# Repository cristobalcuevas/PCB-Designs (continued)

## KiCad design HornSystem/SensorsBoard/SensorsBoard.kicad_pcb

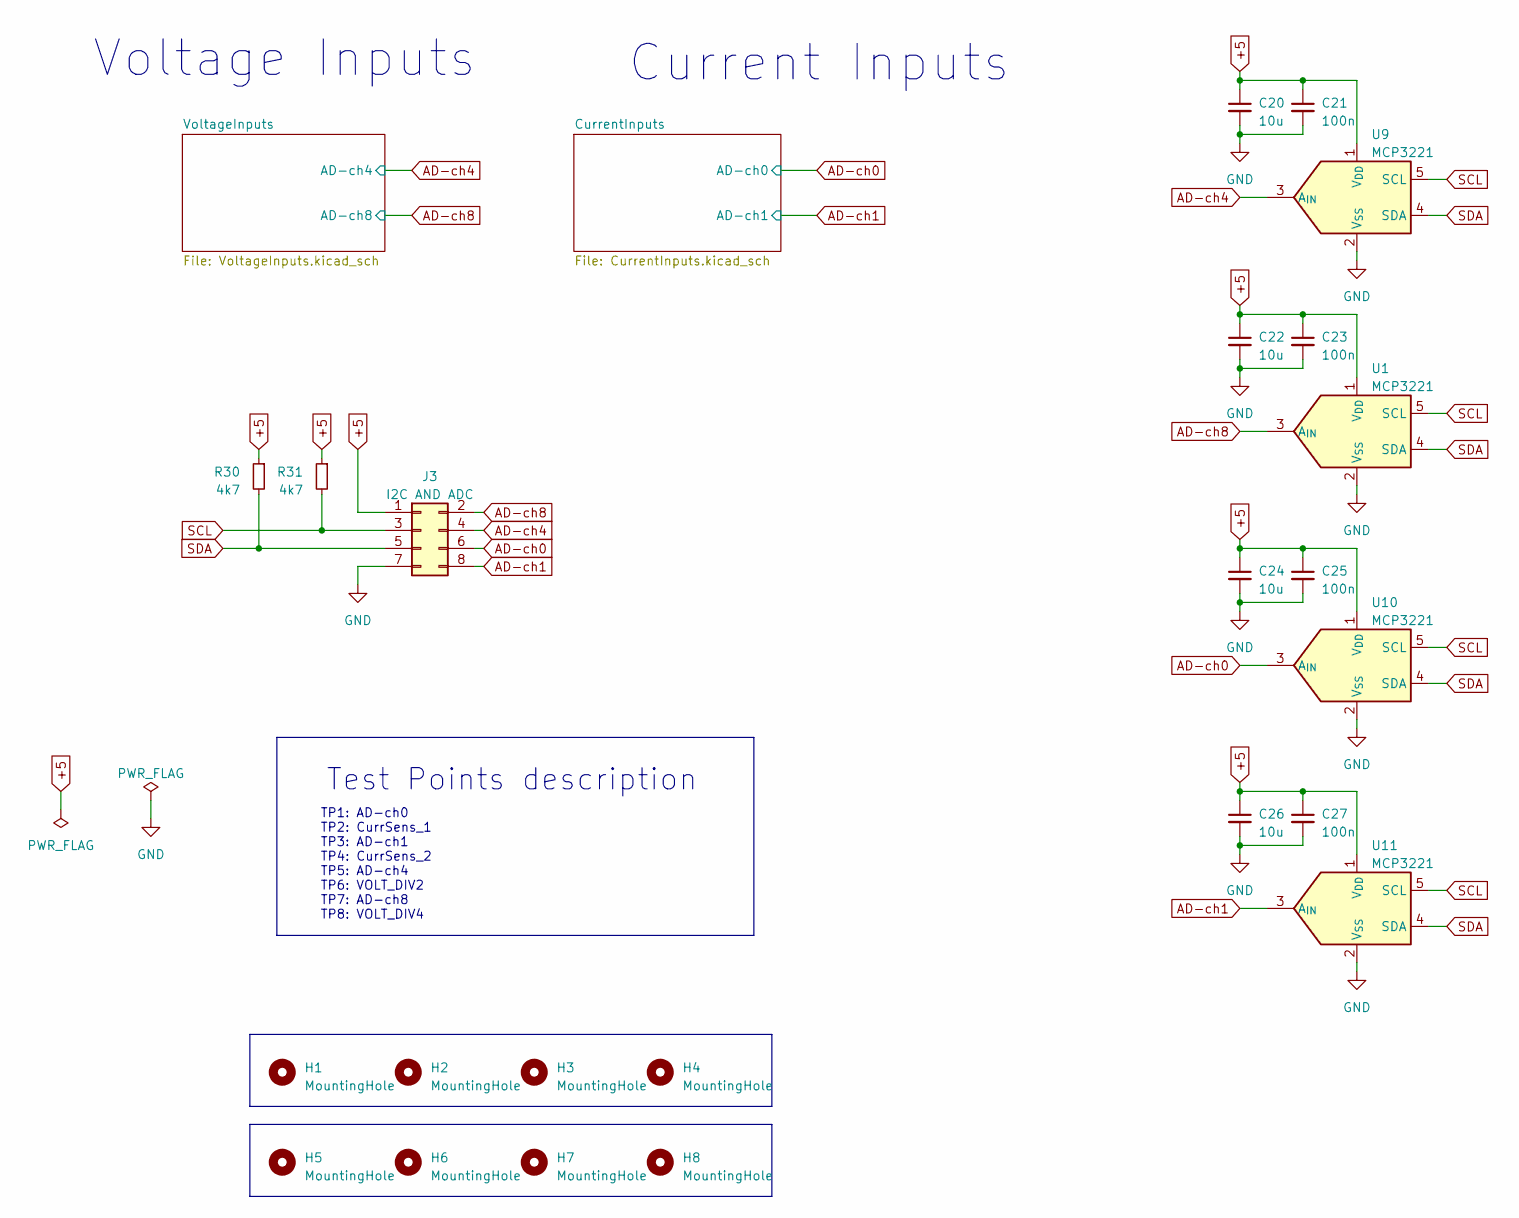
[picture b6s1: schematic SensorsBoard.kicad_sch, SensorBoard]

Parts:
C20, C22, C24, C26: 10u; C_0805_2012Metric; JLCPCB Part C380331
C21, C23, C25, C27: 100n; C_0805_2012Metric; JLCPCB Part C710457
H1, H2, H3, H4, H5, H6, H7, H8: MountingHole; MountingHole_3.2mm_M3
J3: I2C AND ADC; PinHeader_2x04_P2.54mm_Vertical
R30, R31: 4k7; R_0805_2012Metric; JLCPCB Part C2759288
U1, U9, U10, U11: MCP3221; SOT-23-5

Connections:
+5: C20.1, C21.1, C22.1, C23.1, C24.1, C25.1, C26.1, C27.1, J3.1, R30.1, R31.1, U1.1 (V_{DD}), U9.1 (V_{DD}), U10.1 (V_{DD}), U11.1 (V_{DD}); also elsewhere on the board
AD-ch0: J3.6, U10.3 (A_{IN}); also elsewhere on the board
AD-ch1: J3.8, U11.3 (A_{IN}); also elsewhere on the board
AD-ch4: J3.4, U9.3 (A_{IN}); also elsewhere on the board
AD-ch8: J3.2, U1.3 (A_{IN}); also elsewhere on the board
GND: C20.2, C21.2, C22.2, C23.2, C24.2, C25.2, C26.2, C27.2, J3.7, U1.2 (V_{SS}), U9.2 (V_{SS}), U10.2 (V_{SS}), U11.2 (V_{SS}); also elsewhere on the board
SCL: J3.3, R31.2, U1.5 (SCL), U9.5 (SCL), U10.5 (SCL), U11.5 (SCL)
SDA: J3.5, R30.2, U1.4 (SDA), U9.4 (SDA), U10.4 (SDA), U11.4 (SDA)

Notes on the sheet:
Current Inputs
Test Points description
TP1: AD-ch0 TP2: CurrSens_1 TP3: AD-ch1 TP4: CurrSens_2 TP5: AD-ch4 TP6: VOLT_DIV2 TP7: AD-ch8 TP8: VOLT_DIV4
Voltage Inputs

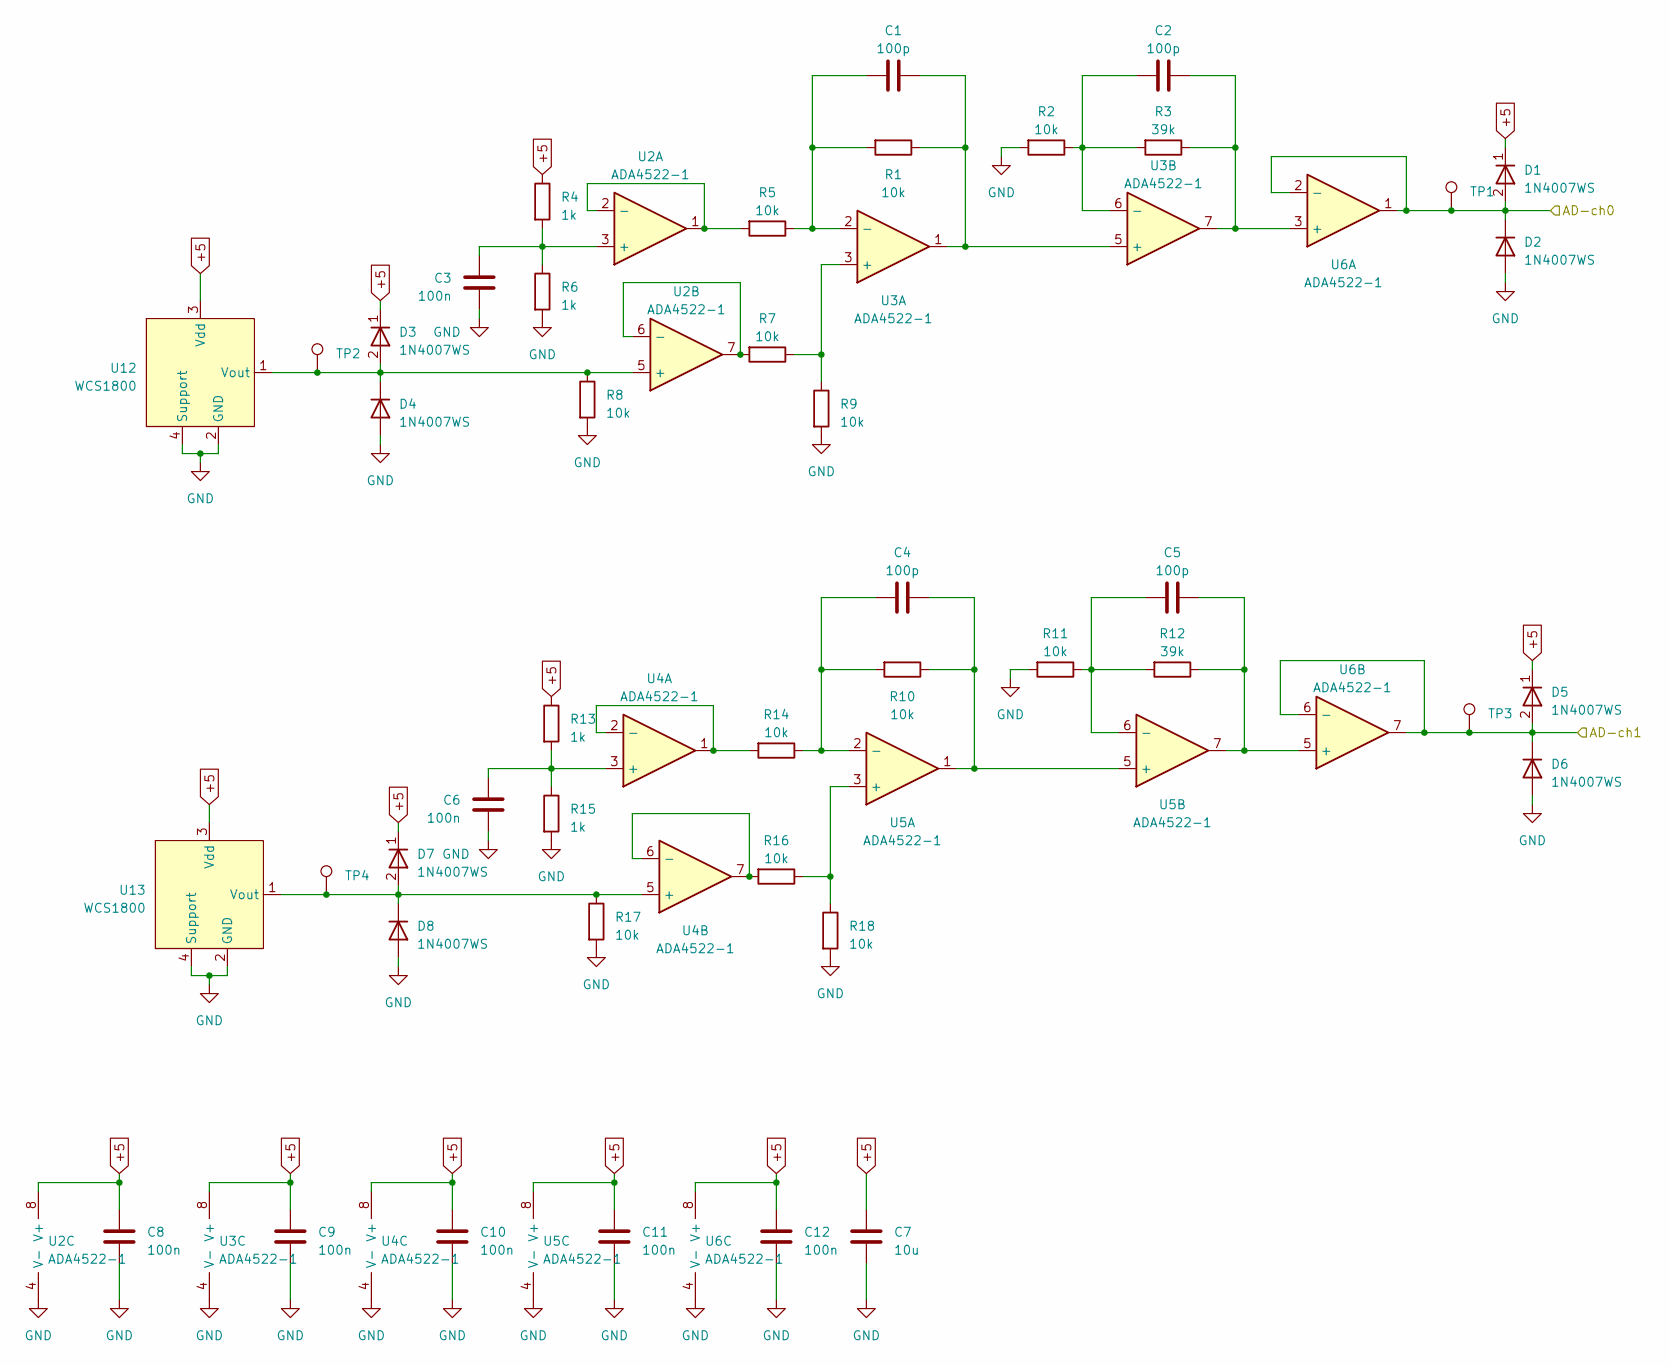
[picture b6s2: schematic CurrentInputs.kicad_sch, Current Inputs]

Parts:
C1, C2, C4, C5: 100p; C_0805_2012Metric; JLCPCB Part C2691714
C3, C6, C8, C9, C10, C11, C12: 100n; C_0805_2012Metric; JLCPCB Part C710457
C7: 10u; C_0805_2012Metric; JLCPCB Part C380331
D1, D2, D3, D4, D5, D6, D7, D8: 1N4007WS; D_SOD-323; JLCPCB Part C193404
R1, R2, R5, R7, R8, R9, R10, R11, R14, R16, R17, R18: 10k; R_0805_2012Metric; JLCPCB Part C212284
R3, R12: 39k; R_0805_2012Metric; JLCPCB Part C139877
R4, R6, R13, R15: 1k; R_0805_2012Metric; JLCPCB Part C335229
TP1, TP2, TP3, TP4: TestPoint; TestPoint_Pad_D1.0mm
U2, U3, U4, U5, U6: ADA4522-1; MSOP-8_3x3mm_P0.65mm; JLCPCB Part C127898
U12, U13: WCS1800

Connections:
+5: C7.1, C8.1, C9.1, C10.1, C11.1, C12.1, D1.1 (K), D3.1 (K), D5.1 (K), D7.1 (K), R4.1, R13.1, U2.8 (V+), U3.8 (V+), U4.8 (V+), U5.8 (V+), U6.8 (V+), U12.3 (Vdd), U13.3 (Vdd); also elsewhere on the board
AD-ch0: D1.2 (A), D2.1 (K), TP1.1, U6.1, U6.2 (-); also elsewhere on the board
AD-ch1: D5.2 (A), D6.1 (K), TP3.1, U6.6 (-), U6.7; also elsewhere on the board
GND: C3.2, C6.2, C7.2, C8.2, C9.2, C10.2, C11.2, C12.2, D2.2 (A), D4.2 (A), D6.2 (A), D8.2 (A), R2.2, R6.2, R8.2, R9.2, R11.2, R15.2, R17.2, R18.2, U2.4 (V-), U3.4 (V-), U4.4 (V-), U5.4 (V-), U6.4 (V-), U12.2 (GND), U12.4 (Support), U13.2 (GND), U13.4 (Support); also elsewhere on the board
unnamed: D3.2 (A), D4.1 (K), R8.1, TP2.1, U2.5 (+), U12.1 (Vout)
unnamed: D7.2 (A), D8.1 (K), R17.1, TP4.1, U4.5 (+), U13.1 (Vout)
unnamed: C3.1, R4.2, R6.1, U2.3 (+)
unnamed: R5.2, U2.1, U2.2 (-)
unnamed: R7.2, U2.6 (-), U2.7
unnamed: R7.1, R9.1, U3.3 (+)
unnamed: C1.1, R1.2, R5.1, U3.2 (-)
unnamed: C1.2, R1.1, U3.1, U3.5 (+)
unnamed: C2.1, R2.1, R3.2, U3.6 (-)
unnamed: C6.1, R13.2, R15.1, U4.3 (+)
unnamed: R14.2, U4.1, U4.2 (-)
unnamed: R16.2, U4.6 (-), U4.7
unnamed: R16.1, R18.1, U5.3 (+)
unnamed: C4.1, R10.2, R14.1, U5.2 (-)
unnamed: C4.2, R10.1, U5.1, U5.5 (+)
unnamed: C5.1, R11.1, R12.2, U5.6 (-)
unnamed: C2.2, R3.1, U3.7, U6.3 (+)
unnamed: C5.2, R12.1, U5.7, U6.5 (+)

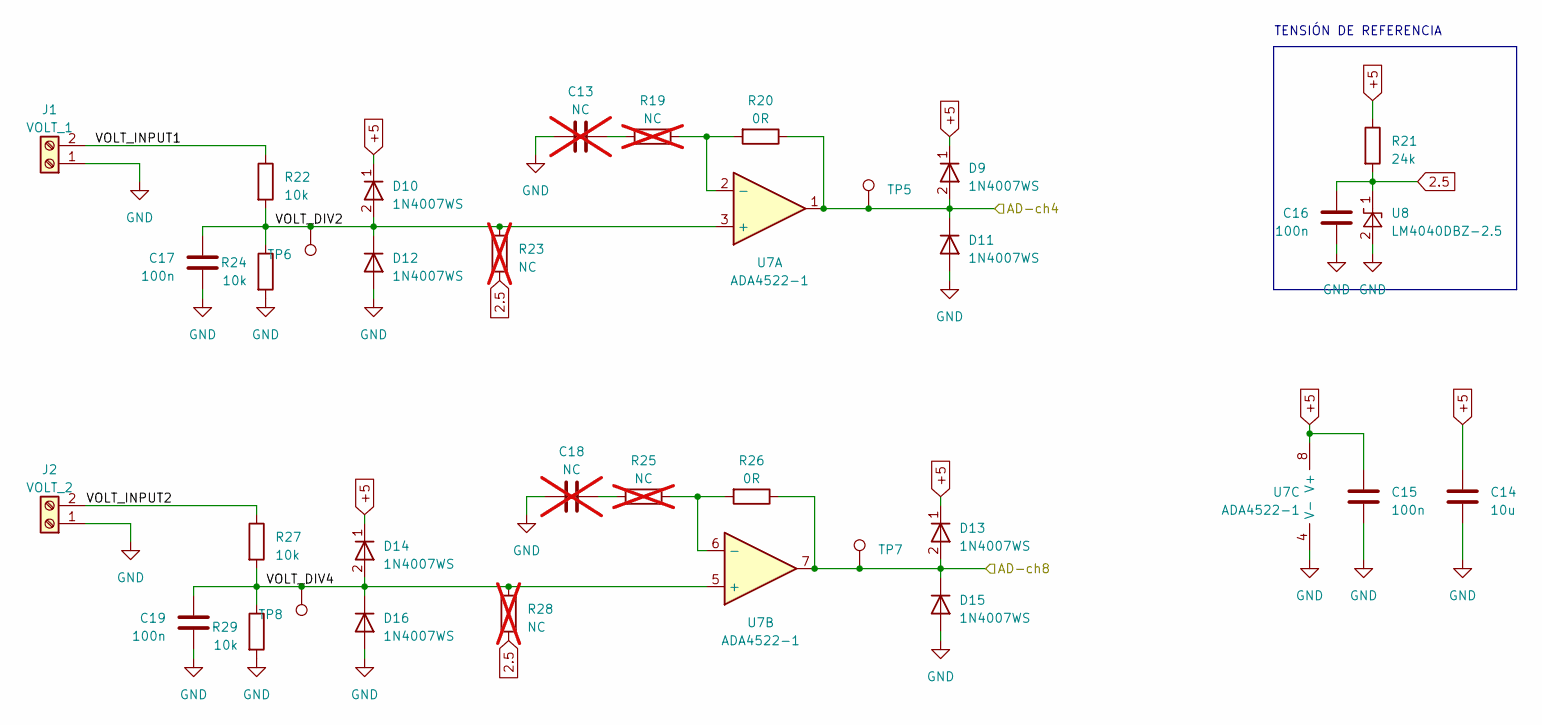
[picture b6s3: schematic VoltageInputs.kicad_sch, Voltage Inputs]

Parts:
C13, C18: NC; C_0805_2012Metric; not fitted
C14: 10u; C_0805_2012Metric; JLCPCB Part C380331
C15, C16, C17, C19: 100n; C_0805_2012Metric; JLCPCB Part C710457
D9, D10, D11, D12, D13, D14, D15, D16: 1N4007WS; D_SOD-323; JLCPCB Part C193404
J1: VOLT_1; TerminalBlock_Phoenix_PT-1,5-2-3.5-H_1x02_P3.50mm_Horizontal; JLCPCB Part C474892
J2: VOLT_2; TerminalBlock_Phoenix_PT-1,5-2-3.5-H_1x02_P3.50mm_Horizontal; JLCPCB Part C474892
R19, R23, R25, R28: NC; R_0805_2012Metric; not fitted
R20, R26: 0R; R_0805_2012Metric; JLCPCB Part C2907288
R21: 24k; R_0805_2012Metric; JLCPCB Part C286604
R22, R24, R27, R29: 10k; R_0805_2012Metric; JLCPCB Part C212284
TP5, TP6, TP7, TP8: TestPoint; TestPoint_Pad_D1.0mm
U7: ADA4522-1; MSOP-8_3x3mm_P0.65mm; JLCPCB Part C127898
U8: LM4040DBZ-2.5; SOT-23; JLCPCB Part C131939

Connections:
2.5: C16.2, R21.2, R23.2, R28.2, U8.1 (K)
+5: C14.1, C15.1, D9.1 (K), D10.1 (K), D13.1 (K), D14.1 (K), R21.1, U7.8 (V+); also elsewhere on the board
/VoltageInputs/VOLT_DIV2: C17.1, D10.2 (A), D12.1 (K), R22.2, R23.1, R24.1, TP6.1, U7.3 (+)
/VoltageInputs/VOLT_DIV4: C19.1, D14.2 (A), D16.1 (K), R27.2, R28.1, R29.1, TP8.1, U7.5 (+)
/VoltageInputs/VOLT_INPUT1: J1.2, R22.1
/VoltageInputs/VOLT_INPUT2: J2.2, R27.1
AD-ch4: D9.2 (A), D11.1 (K), R20.1, TP5.1, U7.1; also elsewhere on the board
AD-ch8: D13.2 (A), D15.1 (K), R26.1, TP7.1, U7.7; also elsewhere on the board
GND: C13.2, C14.2, C15.2, C16.1, C17.2, C18.2, C19.2, D11.2 (A), D12.2 (A), D15.2 (A), D16.2 (A), J1.1, J2.1, R24.2, R29.2, U7.4 (V-), U8.2 (A); also elsewhere on the board
unnamed: C13.1, R19.2
unnamed: C18.1, R25.2
unnamed: R19.1, R20.2, U7.2 (-)
unnamed: R25.1, R26.2, U7.6 (-)

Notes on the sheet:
TENSIÓN DE REFERENCIA

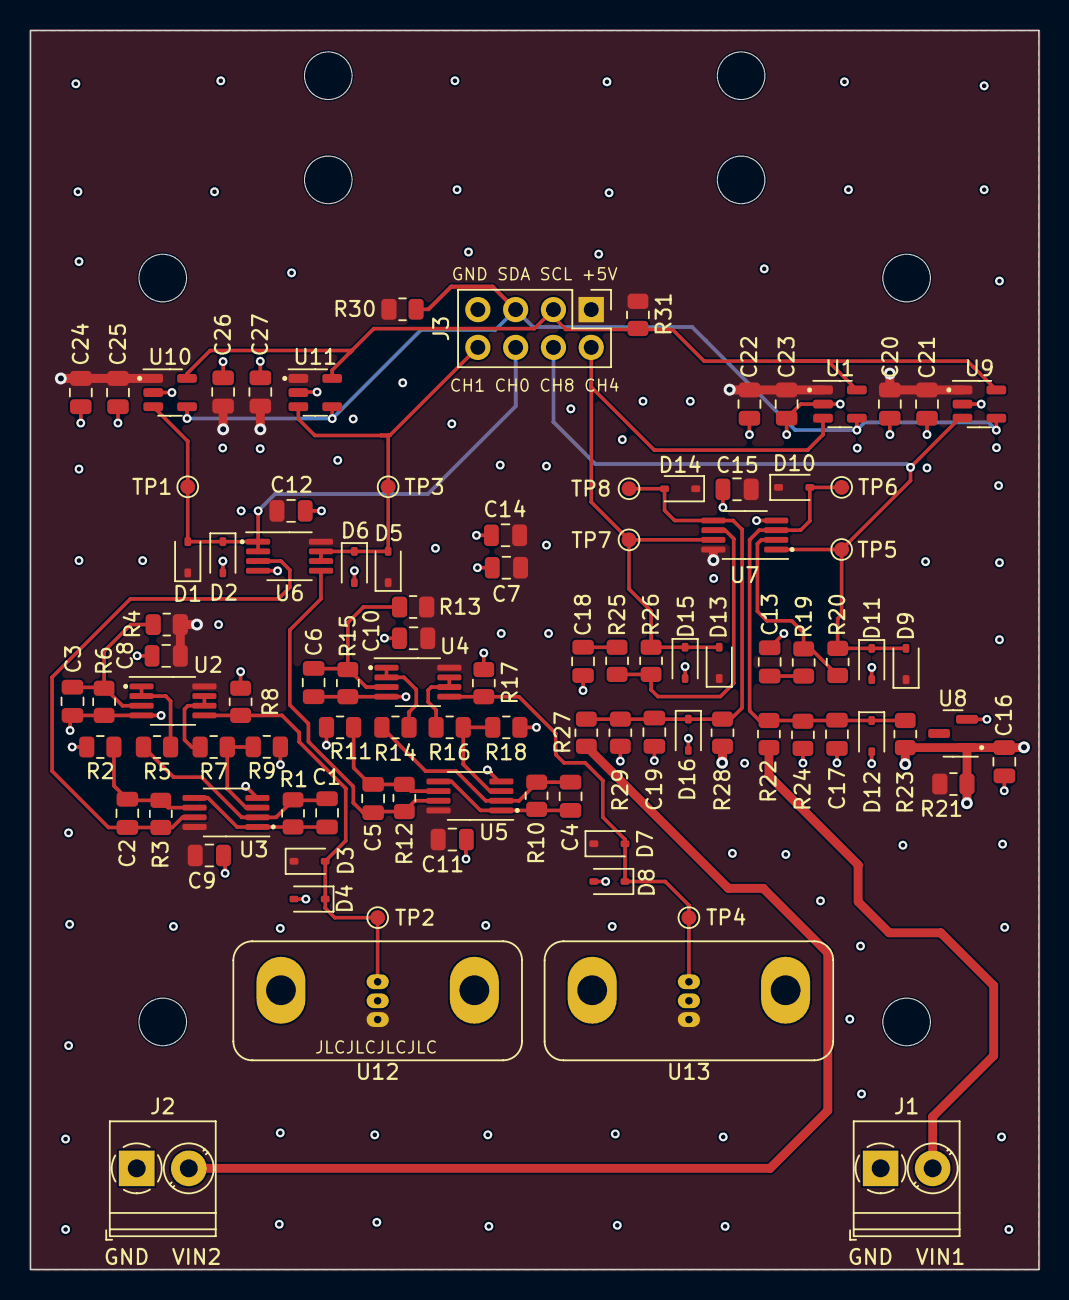
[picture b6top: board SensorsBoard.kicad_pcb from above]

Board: 4 copper layers, 67.8 x 83.3 mm, 106 parts (0 on the bottom side), 35 nets.

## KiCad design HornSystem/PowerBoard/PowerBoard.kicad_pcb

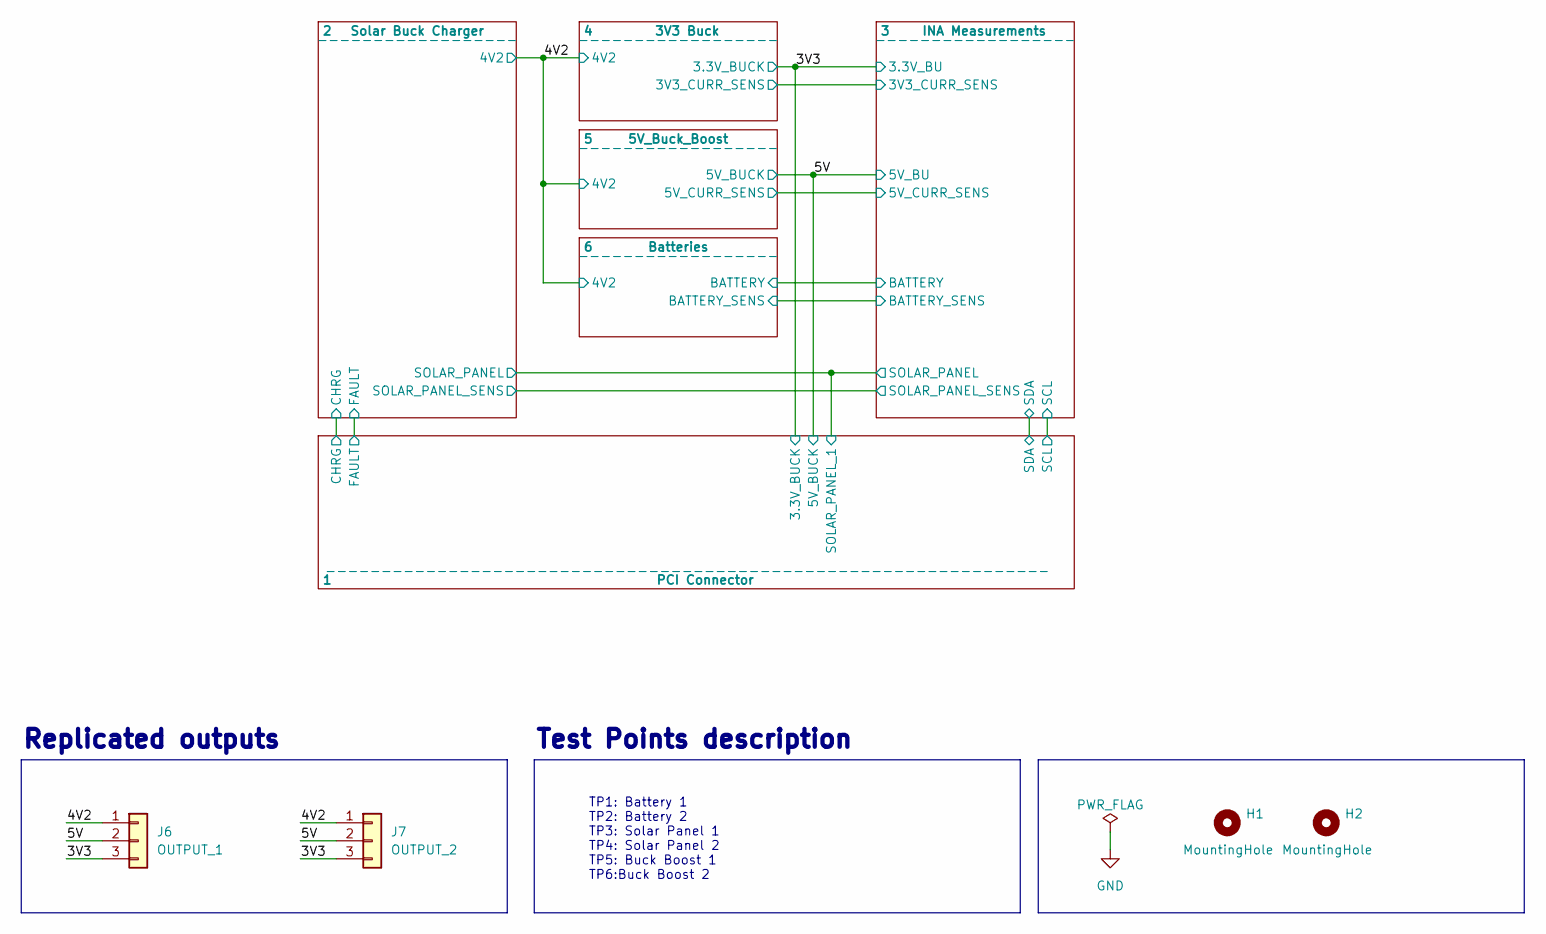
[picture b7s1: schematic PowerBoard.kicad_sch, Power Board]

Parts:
H1, H2: MountingHole; MountingHole_2.1mm
J6: OUTPUT_1; PinHeader_1x03_P2.54mm_Vertical
J7: OUTPUT_2; PinHeader_1x03_P2.54mm_Vertical

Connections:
5V_BUCK: J6.2, J7.2; also elsewhere on the board
/3V3: J6.3, J7.3; also elsewhere on the board
/4V2: J6.1, J7.1; also elsewhere on the board

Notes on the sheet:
TP1: Battery 1 TP2: Battery 2 TP3: Solar Panel 1 TP4: Solar Panel 2 TP5: Buck Boost 1 TP6:Buck Boost 2
Replicated outputs
Test Points description

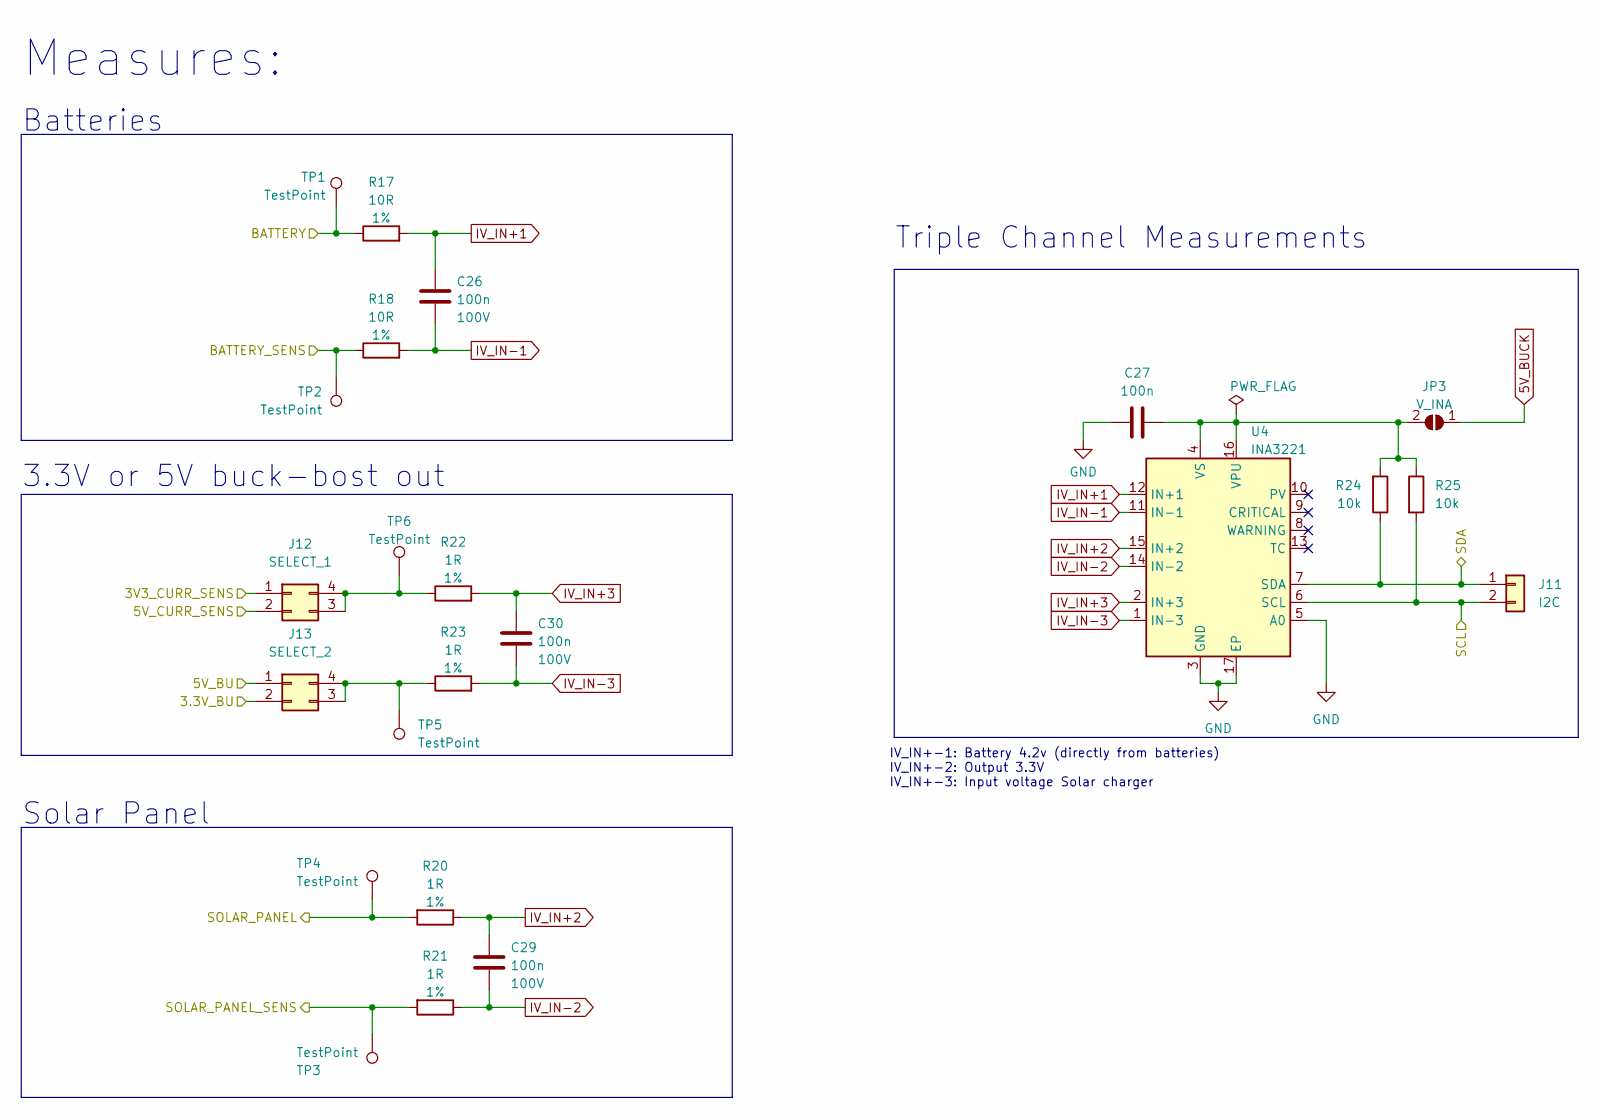
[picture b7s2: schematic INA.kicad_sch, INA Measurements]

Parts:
C26, C27, C29, C30: 100n; C_0805_2012Metric; Voltage 100V; JLCPCB Part C710457
J11: I2C; PinHeader_1x02_P2.54mm_Vertical
J12: SELECT_1; PinHeader_2x02_P2.54mm_Vertical
J13: SELECT_2; PinHeader_2x02_P2.54mm_Vertical
JP3: V_INA; SolderJumper-2_P1.3mm_Open_RoundedPad1.0x1.5mm
R17, R18: 10R; R_0805_2012Metric; Tolerance 1%; JLCPCB Part C17415
R20, R21, R22, R23: 1R; R_0805_2012Metric; Tolerance 1%; JLCPCB Part C25271
R24, R25: 10k; R_0805_2012Metric; JLCPCB Part RMS10FT1002
TP1, TP2, TP3, TP4, TP5, TP6: TestPoint; TestPoint_Pad_D1.0mm
U4: INA3221; Texas_RGV_S-PVQFN-N16_EP2.1x2.1mm; JLCPCB Part C181255

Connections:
5V_BUCK: J13.1, JP3.1 (A); also elsewhere on the board
/3V3: J13.2; also elsewhere on the board
/3V3 Buck/3V3_CURR_SENS: J12.1; also elsewhere on the board
/4V2: R17.1, TP1.1; also elsewhere on the board
/5V_Buck_Boost/5V_CURR_SENS: J12.2; also elsewhere on the board
/Batteries/BATTERY_SENS: R18.1, TP2.1; also elsewhere on the board
/INA Measurements/SCL: J11.2, R25.2, U4.6 (SCL); also elsewhere on the board
/INA Measurements/SDA: J11.1, R24.1, U4.7 (SDA); also elsewhere on the board
/INA Measurements/SOLAR_PANEL: R20.2, TP4.1; also elsewhere on the board
/INA Measurements/SOLAR_PANEL_SENS: R21.2, TP3.1; also elsewhere on the board
GND: C27.2, U4.3 (GND), U4.5 (A0), U4.17 (EP); also elsewhere on the board
IV_IN+1: C26.1, R17.2, U4.12 (IN+1)
IV_IN+2: C29.1, R20.1, U4.15 (IN+2)
IV_IN+3: C30.1, R22.2, U4.2 (IN+3)
IV_IN-1: C26.2, R18.2, U4.11 (IN-1)
IV_IN-2: C29.2, R21.1, U4.14 (IN-2)
IV_IN-3: C30.2, R23.2, U4.1 (IN-3)
unnamed: J12.3, J12.4, R22.1, TP6.1
unnamed: J13.3, J13.4, R23.1, TP5.1
unnamed: C27.1, JP3.2 (B), R24.2, R25.1, U4.4 (VS), U4.16 (VPU)

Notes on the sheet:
Measures:
Triple Channel Measurements
Batteries
IV_IN+-1: Battery 4.2v (directly from batteries) IV_IN+-2: Output 3.3V IV_IN+-3: Input voltage Solar charger
Solar Panel
3.3V or 5V buck-bost out

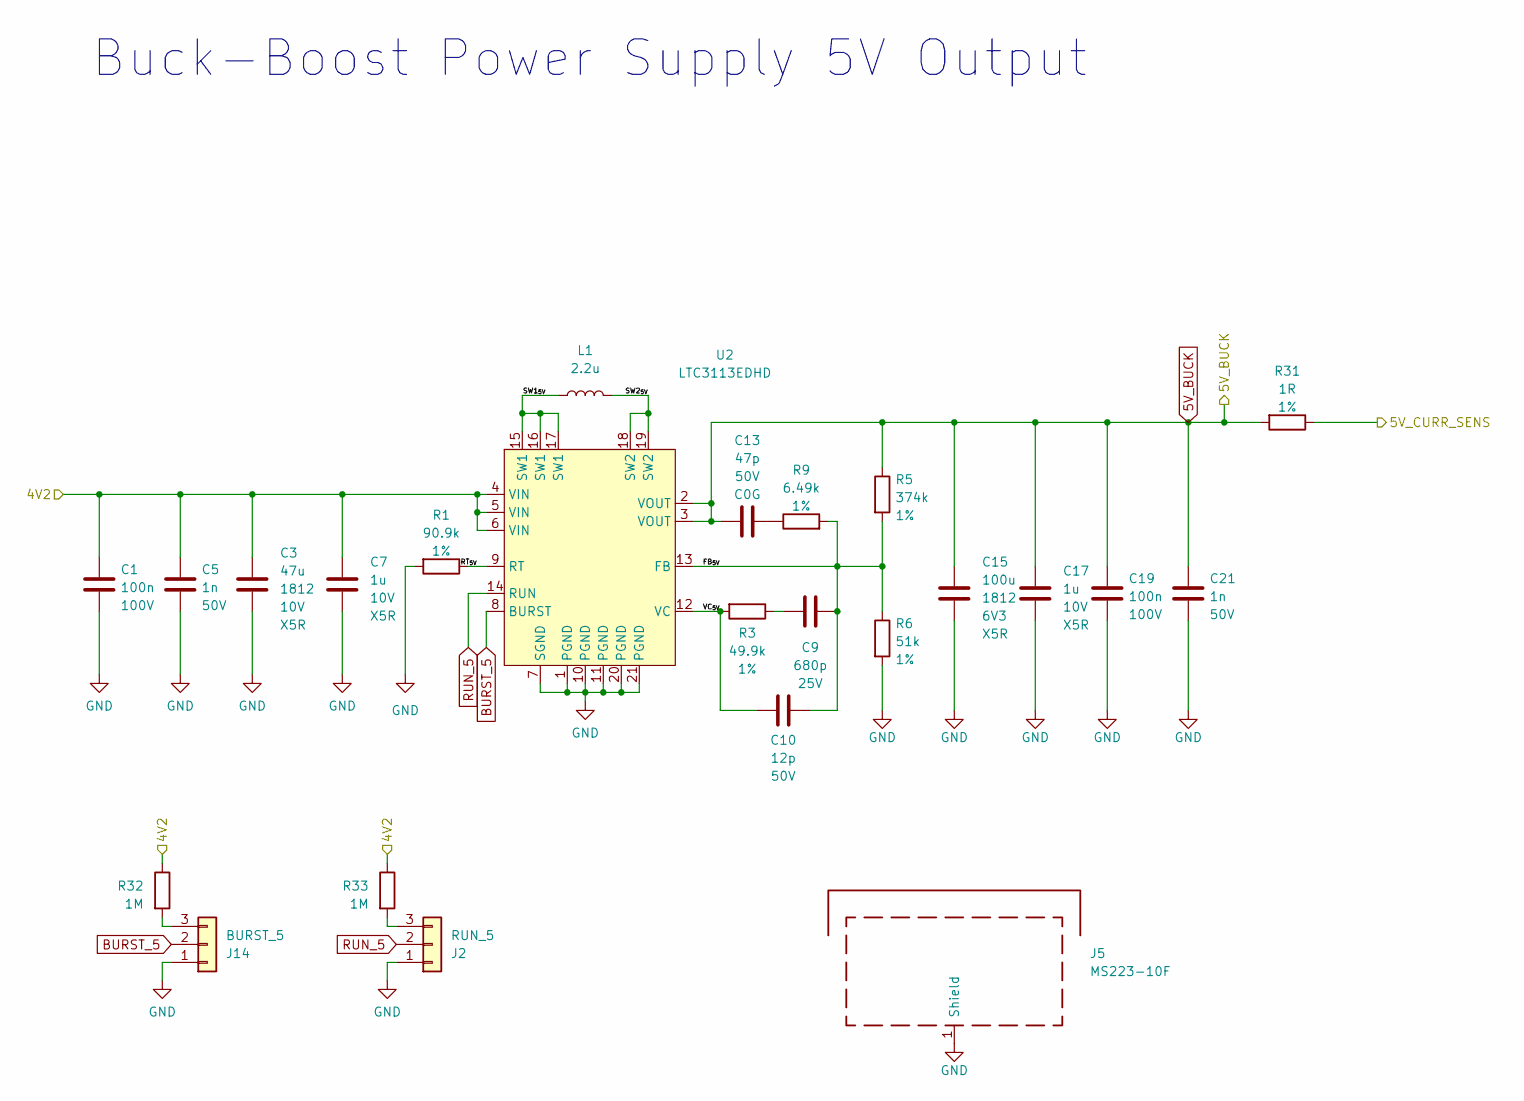
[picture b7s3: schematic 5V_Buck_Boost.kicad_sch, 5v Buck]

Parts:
C1, C19: 100n; C_0805_2012Metric; Voltage 100V; JLCPCB Part C710457
C3: 47u; C_1812_4532Metric; Voltage 10V; JLCPCB Part C24659
C5, C21: 1n; C_0805_2012Metric; Voltage 50V; JLCPCB Part C376917
C7, C17: 1u; C_0805_2012Metric; Voltage 10V; JLCPCB Part C440195
C9: 680p; C_0805_2012Metric; Voltage 25V; JLCPCB Part C520014
C10: 12p; C_0805_2012Metric; Voltage 50V; JLCPCB Part C152848
C13: 47p; C_0805_2012Metric; Voltage 50V; JLCPCB Part C24659
C15: 100u; C_1812_4532Metric; Voltage 6V3; JLCPCB Part C342601
J2: RUN_5; PinHeader_1x03_P2.54mm_Vertical
J5: MS223-10F; Wuerth_36103255_25x25mm; Digikey Part 732-2489-ND
J14: BURST_5; PinHeader_1x03_P2.54mm_Vertical
L1: 2.2u; L_Vishay_IHLP-2525; JLCPCB Part C540967
R1: 90.9k; R_0805_2012Metric; Tolerance 1%; JLCPCB Part C104550
R3: 49.9k; R_0805_2012Metric; Tolerance 1%; JLCPCB Part C17719
R5: 374k; R_0805_2012Metric; Tolerance 1%; JLCPCB Part C273990
R6: 51k; R_0805_2012Metric; Tolerance 1%; JLCPCB Part C17737
R9: 6.49k; R_0805_2012Metric; Tolerance 1%; JLCPCB Part C17769
R31: 1R; R_0805_2012Metric; Tolerance 1%; JLCPCB Part C25271
R32, R33: 1M; R_0805_2012Metric; JLCPCB Part C3152182
U2: LTC3113EDHD; HTSSOP-20-1EP_4.4x6.5mm_P0.65mm_EP2.85x4mm; Digikey Part 505-LTC3113IFE#TRPBFCT-ND

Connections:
5V_BUCK: C13.1, C15.1, C17.1, C19.1, C21.1, R5.1, R31.2, U2.2 (VOUT), U2.3 (VOUT); also elsewhere on the board
/4V2: C1.2, C3.1, C5.1, C7.1, R32.1, R33.1, U2.4 (VIN), U2.5 (VIN), U2.6 (VIN); also elsewhere on the board
/5V_Buck_Boost/5V_CURR_SENS: R31.1; also elsewhere on the board
/5V_Buck_Boost/FB_{5V}: C9.1, C10.1, R5.2, R6.1, R9.2, U2.13 (FB)
/5V_Buck_Boost/RT_{5V}: R1.1, U2.9 (RT)
/5V_Buck_Boost/SW1_{5V}: L1.1, U2.15 (SW1), U2.16 (SW1), U2.17 (SW1)
/5V_Buck_Boost/SW2_{5V}: L1.2, U2.18 (SW2), U2.19 (SW2)
/5V_Buck_Boost/VC_{5V}: C10.2, R3.2, U2.12 (VC)
BURST_5: J14.2, U2.8 (BURST); also elsewhere on the board
GND: C1.1, C3.2, C5.2, C7.2, C15.2, C17.2, C19.2, C21.2, J2.1, J5.1 (Shield), J14.1, R1.2, R6.2, U2.1 (PGND), U2.7 (SGND), U2.10 (PGND), U2.11 (PGND), U2.20 (PGND), U2.21 (PGND); also elsewhere on the board
unnamed: C9.2, R3.1
unnamed: C13.2, R9.1
unnamed: J2.3, R33.2
unnamed: J14.3, R32.2
RUN_5: J2.2, U2.14 (RUN); also elsewhere on the board

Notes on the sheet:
Buck-Boost Power Supply 5V Output

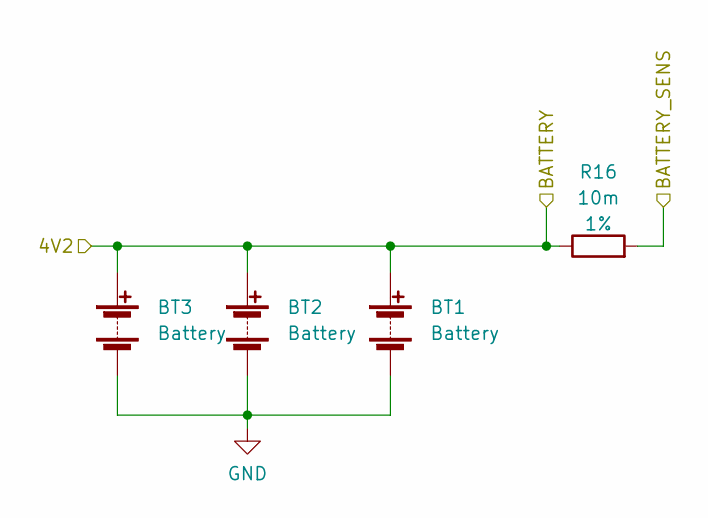
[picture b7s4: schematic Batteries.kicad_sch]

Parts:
BT1, BT2, BT3: Battery; BatteryHolder_MPD_BH-18650-PC2; Digikey Part BH-18650-PC
R16: 10m; R_0805_2012Metric; Tolerance 1%; JLCPCB Part C473034

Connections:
/4V2: BT1.1 (+), BT2.1 (+), BT3.1 (+), R16.1; also elsewhere on the board
/Batteries/BATTERY_SENS: R16.2; also elsewhere on the board
GND: BT1.2 (-), BT2.2 (-), BT3.2 (-); also elsewhere on the board

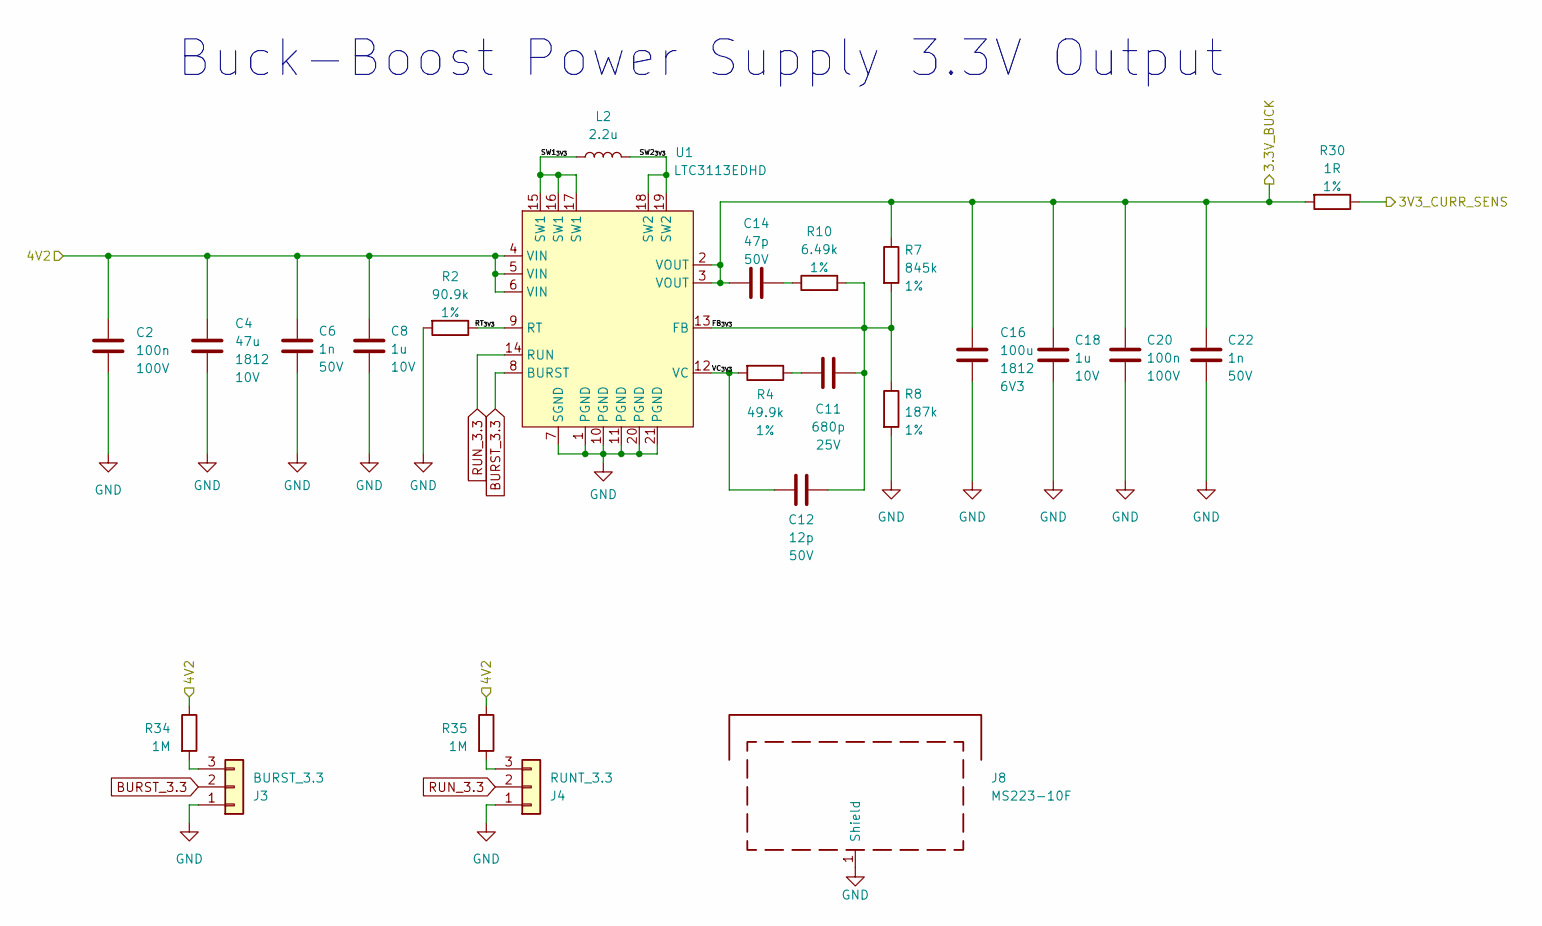
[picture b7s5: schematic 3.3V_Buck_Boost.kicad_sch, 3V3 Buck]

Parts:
C2, C20: 100n; C_0805_2012Metric; Voltage 100V; JLCPCB Part C710457
C4: 47u; C_1812_4532Metric; Voltage 10V; JLCPCB Part C24659
C6, C22: 1n; C_0805_2012Metric; Voltage 50V; JLCPCB Part C376917
C8, C18: 1u; C_0805_2012Metric; Voltage 10V; JLCPCB Part C440195
C11: 680p; C_0805_2012Metric; Voltage 25V; JLCPCB Part C520014
C12: 12p; C_0805_2012Metric; Voltage 50V; JLCPCB Part C152848
C14: 47p; C_0805_2012Metric; Voltage 50V; JLCPCB Part C24659
C16: 100u; C_1812_4532Metric; Voltage 6V3; JLCPCB Part C342601
J3: BURST_3.3; PinHeader_1x03_P2.54mm_Vertical
J4: RUNT_3.3; PinHeader_1x03_P2.54mm_Vertical
J8: MS223-10F; Wuerth_36103255_25x25mm; Digikey Part 732-2489-ND
L2: 2.2u; L_Vishay_IHLP-2525; JLCPCB Part C540967
R2: 90.9k; R_0805_2012Metric; Tolerance 1%; JLCPCB Part C104550
R4: 49.9k; R_0805_2012Metric; Tolerance 1%; JLCPCB Part C17719
R7: 845k; R_0805_2012Metric; Tolerance 1%; JLCPCB Part C274004
R8: 187k; R_0805_2012Metric; Tolerance 1%; JLCPCB Part C334880
R10: 6.49k; R_0805_2012Metric; Tolerance 1%; JLCPCB Part C17769
R30: 1R; R_0805_2012Metric; Tolerance 1%; JLCPCB Part C25271
R34, R35: 1M; R_0805_2012Metric; JLCPCB Part C3152182
U1: LTC3113EDHD; HTSSOP-20-1EP_4.4x6.5mm_P0.65mm_EP2.85x4mm; Digikey Part 505-LTC3113IFE#TRPBFCT-ND

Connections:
/3V3: C14.1, C16.1, C18.1, C20.1, C22.1, R7.1, R30.2, U1.2 (VOUT), U1.3 (VOUT); also elsewhere on the board
/3V3 Buck/3V3_CURR_SENS: R30.1; also elsewhere on the board
/3V3 Buck/FB_{3V3}: C11.1, C12.1, R7.2, R8.1, R10.2, U1.13 (FB)
/3V3 Buck/RT_{3V3}: R2.1, U1.9 (RT)
/3V3 Buck/SW1_{3V3}: L2.1, U1.15 (SW1), U1.16 (SW1), U1.17 (SW1)
/3V3 Buck/SW2_{3V3}: L2.2, U1.18 (SW2), U1.19 (SW2)
/3V3 Buck/VC_{3V3}: C12.2, R4.2, U1.12 (VC)
/4V2: C2.2, C4.1, C6.1, C8.1, R34.1, R35.1, U1.4 (VIN), U1.5 (VIN), U1.6 (VIN); also elsewhere on the board
BURST_3.3: J3.2, U1.8 (BURST); also elsewhere on the board
GND: C2.1, C4.2, C6.2, C8.2, C16.2, C18.2, C20.2, C22.2, J3.1, J4.1, J8.1 (Shield), R2.2, R8.2, U1.1 (PGND), U1.7 (SGND), U1.10 (PGND), U1.11 (PGND), U1.20 (PGND), U1.21 (PGND); also elsewhere on the board
unnamed: C11.2, R4.1
unnamed: C14.2, R10.1
unnamed: J3.3, R34.2
unnamed: J4.3, R35.2
RUN_3.3: J4.2, U1.14 (RUN); also elsewhere on the board

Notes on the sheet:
Buck-Boost Power Supply 3.3V Output

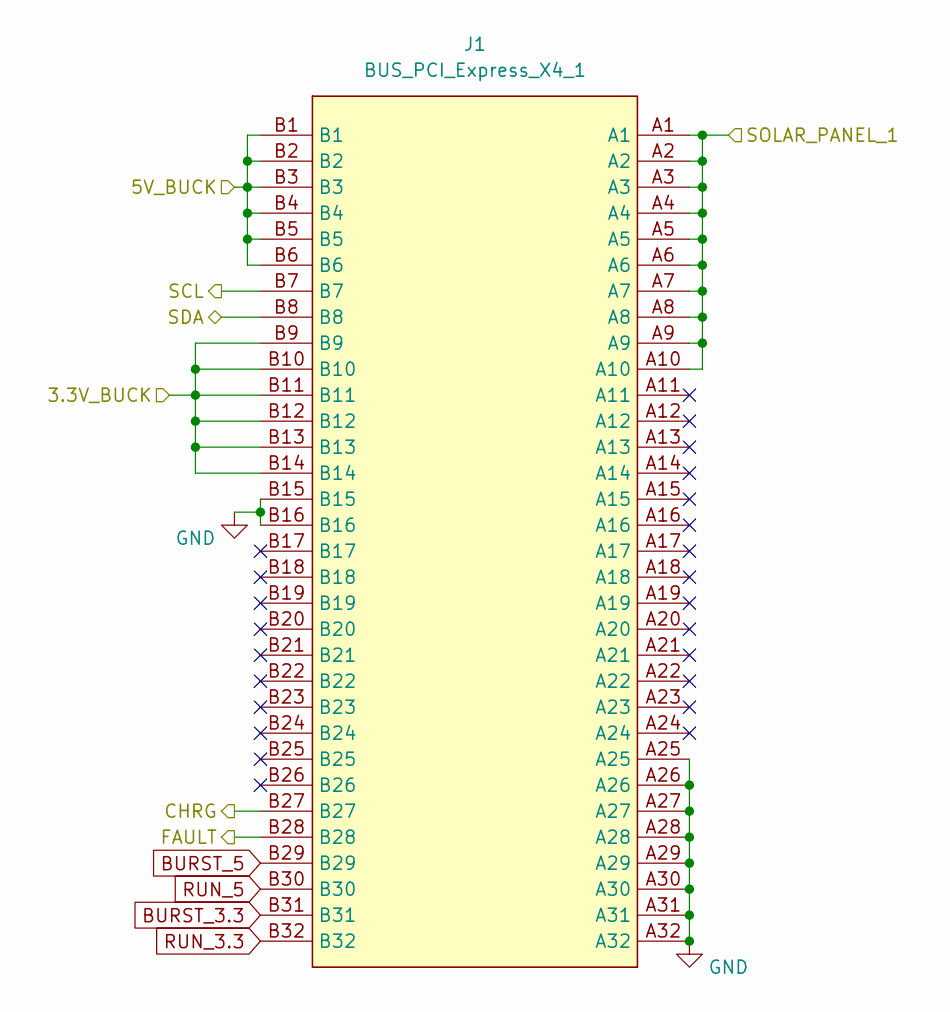
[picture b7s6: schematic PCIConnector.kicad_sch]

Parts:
J1: BUS_PCI_Express_X4_1; BUS_PCIexpress_x4

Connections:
5V_BUCK: J1.B1, J1.B2, J1.B3, J1.B4, J1.B5, J1.B6; also elsewhere on the board
/3V3: J1.B9, J1.B10, J1.B11, J1.B12, J1.B13, J1.B14; also elsewhere on the board
/INA Measurements/SCL: J1.B7; also elsewhere on the board
/INA Measurements/SDA: J1.B8; also elsewhere on the board
/INA Measurements/SOLAR_PANEL: J1.A1, J1.A2, J1.A3, J1.A4, J1.A5, J1.A6, J1.A7, J1.A8, J1.A9, J1.A10; also elsewhere on the board
/PCI Connector/CHRG: J1.B27; also elsewhere on the board
/PCI Connector/FAULT: J1.B28; also elsewhere on the board
BURST_3.3: J1.B31; also elsewhere on the board
BURST_5: J1.B29; also elsewhere on the board
GND: J1.A25, J1.A26, J1.A27, J1.A28, J1.A29, J1.A30, J1.A31, J1.A32, J1.B15, J1.B16; also elsewhere on the board
RUN_3.3: J1.B32; also elsewhere on the board
RUN_5: J1.B30; also elsewhere on the board
